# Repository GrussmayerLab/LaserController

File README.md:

# Laser Controller Project

## TL;DR (Quick Setup)

1. **Assemble the PCB**: 
   - Order the PCB from [JLCPCB](https://cart.jlcpcb.com) for ~$100 using the `gerber.zip`, `bom.csv`, and `laser_controller-top-pos.csv` files.
   - Use compatible [JST cables](https://www.amazon.nl/-/en/Mini-Micro-150mm-Cable-Female/dp/B01DU9OY40).

2. **Install MicroManager 2.0**:
   - Download and install [MicroManager 2.0](https://download.micro-manager.org/nightly/2.0/Windows/).

3. **Copy Files**:
   - Copy the precompiled `EMU` folder and `mmgr_dal_GrussmayerLab-LaserController.dll` into the root directory of MicroManager.

4. **Use the LaserControlGUI Plugin**:
   - Run MicroManager, open the **LaserControlGUI** plugin from **EMU**, and start controlling the laser!

---

This repository consists of the hardware, firmware, and software design for the Laser Controller system. It is divided into four main sections:

- **Electronics**: Schematic and PCB design files for the laser controller.
- **LaserControlFirmware**: C/C++ firmware for the Raspberry Pi Pico.
- **GrussmayerLab-LaserController**: C++ Micromanager Device Adapter to drive the laser controller.
- **LaserControlGUI**: Java-based plugin for Micromanager, built upon the EMU plugin.

## Table of Contents

- [Overview](#overview)
- [Folders](#folders)
  - [Electronics](#electronics)
  - [LaserControlFirmware](#lasercontrolfirmware)
  - [LaserControllerUI](#lasercontrollerui)
- [Getting Started](#getting-started)
  - [Hardware Setup](#hardware-setup)
  - [Firmware Setup](#firmware-setup)
  - [Software Setup](#software-setup)
- [Usage](#usage)
- [Contributing](#contributing)
- [License](#license)

## Overview

The Laser Controller project integrates hardware and software components to control a laser system. It consists of:

1. **Hardware**: Electronics, including a schematic and PCB design, for laser control.
2. **Firmware**: Raspberry Pi Pico firmware (C/C++) managing communication with the hardware.
3. **Software**: A Java plugin for MicroManager, based on the EMU plugin framework, along with a C++ Device Adapter for MicroManager.

## Folders

### Electronics

This folder contains the hardware designs for the laser controller:

- **Schematic**: Electrical design for the laser control system.
- **PCB Design**: Printed circuit board design files created using KiCAD.

Files in this folder:
- `schematic.kicad_sch`: Schematic file.
- `pcb.kicad_pcb`: PCB design file.

For more details, refer to the [KiCAD Documentation](https://kicad.org/documentation/).

### LaserControlFirmware

Firmware for the Raspberry Pi Pico, written in C/C++, responsible for controlling the laser system.

Files in this folder:
- `main.cpp`: Main program code.
- `CMakeLists.txt`: CMake configuration.
- `README.md`: Firmware setup instructions.

### LaserControlGUI

Java-based plugin for Micromanager, allowing control of the laser system.

Files in this folder:
- `LaserPanel.java`: Laser slide panel code.
- `MyFrame.java`: Main plugin UI containing multiple LaserPanel instances.
- `MyPlugin.java`: Main plugin class implementing the UIPlugin interface.

## Getting Started

### Hardware Setup

1. **Review Hardware Files**: Use KiCAD to view schematic and PCB design files in the `Electronics` folder.
2. **Assemble the PCB**: Using `gerber.zip`, `bom.csv`, and `laser_controller-top-pos.csv`, you can assemble your PCB at [JLCPCB](https://cart.jlcpcb.com) for approximately $100.
3. **Connect Components**: The board has **JST S3B-PH-K-S (LF)(SN)** connectors. Buy [compatible cables](https://www.amazon.nl/-/en/Mini-Micro-150mm-Cable-Female/dp/B01DU9OY40) and modify them as needed.

### Firmware Setup

1. **Flashing Precompiled Firmware**:
   - The compiled UF2 firmware is already included in the repository.
   - Hold the **BOOTSEL** button on the Raspberry Pi Pico, connect it to a PC via USB, and it will appear as a **USB drive**.
   - Copy the UF2 file to the drive, and the Pico is programmed.

2. **Optional: Building from Source**:
   If you wish to modify the firmware, install the following tools:
   - [Raspberry Pi Pico SDK](https://github.com/raspberrypi/pico-sdk)
   - [CMake](https://cmake.org/)
   - [ARM GCC Toolchain](https://developer.arm.com/tools-and-software/openSourceTools/gnu-toolchain/gnu-toolchain-r)

   Clone the repository and build:
   ```bash
   git clone https://github.com/GrussmayerLab/LaserController.git
   cd LaserControlFirmware
   mkdir build
   cd build
   cmake ..
   make
   ```

### Software Setup

1. **Install MicroManager 2.0**:
   - Download and install the latest version of [MicroManager 2.0](https://download.micro-manager.org/nightly/2.0/Windows/). Copy the precompiled `EMU` folder (provided) into the root directory of MicroManager.

2. **Install the EMU Plugin** (for source code editing):
   - If you wish to modify or extend the plugin, follow the instructions on how to install [EMU](https://jdeschamps.github.io/EMU-guide/):

3. **Install LaserControlGUI Plugin**:
   - To enable the LaserControlUI plugin, export the Java project from Eclipse into the EMU folder in MicroManager.

4. **Install the Device Adapter**:
   - Copy the `mmgr_dal_GrussmayerLab-LaserController.dll` file in the root directory of MicroManager.
   - If you need to configure or extend the device adapter, follow the [MicroManager Visual Studio setup guide](https://micro-manager.org/Visual_Studio_project_settings_for_device_adapters). After setting up your project, place `.h` files in the header folder and `.cpp` files in the source folder. Compile the project, and place the resulting `.dll` file in the root directory of MicroManager.

## Usage

1. Start MicroManager.
2. Open the **LaserControlGUI** plugin.
3. The plugin will interface with the Raspberry Pi Pico, allowing laser control via MicroManager.

## License

This project is licensed under the MIT License - see the LICENSE file for details.

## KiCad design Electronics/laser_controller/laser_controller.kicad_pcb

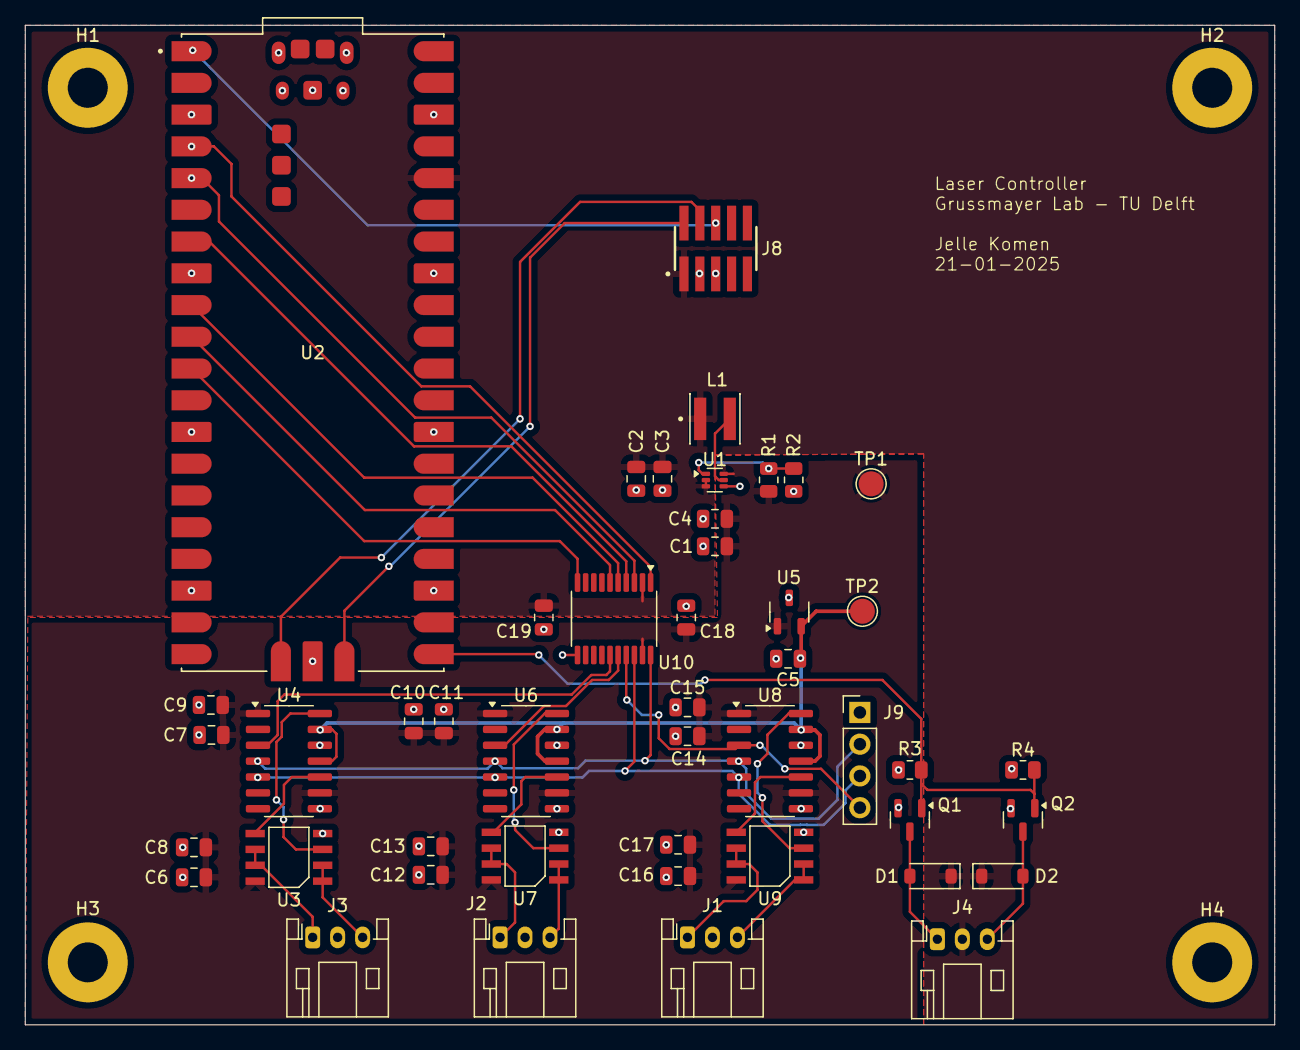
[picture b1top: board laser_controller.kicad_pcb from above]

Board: 2 copper layers, 100.0 x 80.0 mm, 50 parts (0 on the bottom side), 35 nets.

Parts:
C1, C3, C4, C5, C8, C9, C10, C12, C14, C16: 10u; C_0805_2012Metric
C2, C6, C7, C11, C13, C15, C17, C18, C19: 100n; C_0805_2012Metric
D1, D2: SM4007PL; D_SOD-123
H1, H2, H3, H4: MountingHole_Pad; MountingHole_3.2mm_M3_Pad
J1, J2, J3, J4: S3B-PH-K-S_LF__SN_; JST_PH_S3B-PH-K_1x03_P2.00mm_Horizontal
J8: FTSH-105-01-F-DV-P-TR; SAMTEC_FTSH-105-01-F-DV-P-TR
J9: Conn_01x04_Pin; PinHeader_1x04_P2.54mm_Vertical
L1: XEL4030-102MEC; IND_XEL4030-102MEC
Q1, Q2: AO3400A; SOT-23
R1: 820k; R_0805_2012Metric
R2: 100k; R_0805_2012Metric
R3, R4: 10k; R_0805_2012Metric
TP1: TEST +5V5; TestPoint_Pad_D2.0mm
TP2: TEST +2V5; TestPoint_Pad_D2.0mm
U1: TPS61023; SOT-563
U2: SC0915; MODULE_SC0915
U3, U7, U9: MCP6022; SOIC-8-SN
U4, U6, U8: MCP4922-ESL; SOIC-14_3.9x8.7mm_P1.27mm
U5: REF3025-AIDBZR; SOT-23-3
U10: TXS0108EPW; Texas_PW0020A_TSSOP-20_4.4x6.5mm_P0.65mm

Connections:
+2V5: C5.1, TP2.1, U4.11 (VrefB), U4.13 (VrefA), U5.2 (OUT), U6.11 (VrefB), U6.13 (VrefA), U8.11 (VrefB), U8.13 (VrefA)
+3.3V: C2.1, C3.1, C19.1, D1.1 (K), D2.1 (K), J4.2, J8.01, L1.1, U1.2 (EN), U1.3 (VIN), U2.36 (3V3_OUT), U10.2 (VCCA)
CLK: U2.4 (GP2), U10.1 (A1)
CLK_B: J9.2, U4.4 (SCK), U6.4 (SCK), U8.4 (SCK), U10.20 (B1)
CS_A: U2.7 (GP5), U10.4 (A3)
CS_A_B: J9.4, U8.3 (~CS), U10.17 (B3)
CS_B: U2.9 (GP6), U10.5 (A4)
CS_B_B: U6.3 (~CS), U10.16 (B4)
CS_C: U2.10 (GP7), U10.6 (A5)
CS_C_B: U4.3 (~CS), U10.15 (B5)
DAC_A0: J1.3, U9.1, U9.2 (-)
DAC_A1: J1.1, U9.6 (-), U9.7
DAC_B0: J2.3, U7.1, U7.2 (-)
DAC_B1: J2.1, U7.6 (-), U7.7
DAC_C0: J3.3, U3.1, U3.2 (-)
DAC_C1: J3.1, U3.6 (-), U3.7
GND: C1.2, C2.2, C3.2, C4.2, C5.2, C6.2, C7.2, C8.2, C9.2, C10.2, C11.2, C12.2, C13.2, C14.2, C15.2, C16.2, C17.2, C18.2, C19.2, H1.1, H2.1, H3.1, H4.1, J1.2, J2.2, J3.2, J8.03, J8.05, J9.1, Q1.2 (S), Q2.2 (S), R2.2, R3.2, R4.2, U1.4 (GND), U2.3 (GND), U2.8 (GND), U2.13 (GND), U2.18 (GND), U2.23 (GND), U2.28 (GND), U2.33 (AGND), U2.38 (GND), U2.A (USB_SHIELD), U2.B (USB_SHIELD), U2.C (USB_SHIELD), U2.D (USB_SHIELD), U2.D2 (GND), U2.TP1 (TP1_GND), U3.4 (V-), U4.8 (~LDAC), U4.12 (AVSS), U5.3 (GND), U6.8 (~LDAC), U6.12 (AVSS), U7.4 (V-), U8.8 (~LDAC), U8.12 (AVSS), U9.4 (V-), U10.11 (GND)
MOSI: U2.5 (GP3), U10.3 (A2)
MOSI_B: J9.3, U4.5 (SDI), U6.5 (SDI), U8.5 (SDI), U10.18 (B2)
Motor- A: D1.2 (A), J4.1, Q1.3 (D)
Motor- B: D2.2 (A), J4.3, Q2.3 (D)
unnamed: R1.2, R2.1, U1.1 (FB)
unnamed: L1.2, U1.5 (SW)
unnamed: U3.3 (+), U4.14 (VoutA)
unnamed: U3.5 (+), U4.10 (VoutB)
unnamed: U6.14 (VoutA), U7.3 (+)
unnamed: U6.10 (VoutB), U7.5 (+)
unnamed: U8.14 (VoutA), U9.3 (+)
unnamed: U8.10 (VoutB), U9.5 (+)
OE: U2.11 (GP8), U10.10 (OE)
PWM: Q1.1 (G), Q2.1 (G), R3.1, R4.1, U2.21 (GP16)
SWDCLK: J8.04, U2.D1 (SWCLK)
SWDIO: J8.02, U2.D3 (SWDIO)
SWO: J8.06, U2.1 (GP0)
VCC: C1.1, C4.1, C6.1, C7.1, C8.1, C9.1, C10.1, C11.1, C12.1, C13.1, C14.1, C15.1, C16.1, C17.1, C18.1, R1.1, TP1.1, U1.6 (VOUT), U3.8 (V+), U4.1 (VDD), U4.9 (~SHDN), U5.1 (IN), U6.1 (VDD), U6.9 (~SHDN), U7.8 (V+), U8.1 (VDD), U8.9 (~SHDN), U9.8 (V+), U10.19 (VCCB)

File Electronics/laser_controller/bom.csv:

"Comment","Designator","Footprint","LCSC"
"TXS0108EPW", "U10", "Package_SO:Texas_PW0020A_TSSOP-20_4.4x6.5mm_P0.65mm", "C17206"
"REF3025-AIDBZR","U5","Package_TO_SOT_SMD:SOT-23-3","C11334"
"MCP4922-ESL","U4,U6,U8","Package_SO:SOIC-14_3.9x8.7mm_P1.27mm","C39851"
"MCP6022","U3,U7,U9","Package_SO:SOIC-8_5.275x5.275mm_P1.27mm","C57639"
"TPS61023","U1","Package_TO_SOT_SMD:SOT-563","C919459"
"10k","R3,R4","Resistor_SMD:R_0805_2012Metric","C149504"
"100k","R2","Resistor_SMD:R_0805_2012Metric","C441992"
"820k","R1","Resistor_SMD:R_0805_2012Metric","C413229"
"AO3400A","Q1,Q2","Package_TO_SOT_SMD:SOT-23","C20917"
"XEL4030-102MEC","L1","parts:IND_XEL4030-102MEC","C5441341"
"FTSH-105-01-F-DV-P-TR","J8","parts:SAMTEC_FTSH-105-01-F-DV-P-TR","C5136979"
"SM4007PL","D1,D2","Diode_SMD:D_SOD-123","C64898"
"100n","C2,C6,C7,C11,C13,C15,C17,C18,C19","Capacitor_SMD:C_0805_2012Metric","C1711"
"10u","C1,C3,C4,C5,C8,C9,C10,C12,C14,C16","Capacitor_SMD:C_0805_2012Metric","C1713"
"S3B-PH-K-S_LF__SN_", "J1,J2,J3,J4","Connector_JST:JST_PH_S3B-PH-K_1x03_P2.00mm_Horizontal","C157929"

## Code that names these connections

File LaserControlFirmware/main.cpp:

#include "mcp4922.h"
#include <hardware/spi.h>
#include <hardware/pwm.h>
#include <stdio.h>
#include "pico/stdlib.h"
#include <string.h> // For memset

#define CLk_FREQ 100000
#define SCLK 2
#define MOSI 3
#define CS_C 5
#define CS_B 6
#define CS_A 7
#define OE 8
#define PWM 16
#define CMD_GET_DEVICE 0x01
#define CMD_SET_LASER 0x02
#define CMD_SET_MOTOR 0x03

#define START_FLAG 0x7E
#define END_FLAG 0x7F
#define DEVICE_ID 0x01
#define RESPONSE_ERROR 0xFF
#define BUFFER_SIZE 64
#define QUEUE_SIZE 10 // Number of messages in FIFO

// FIFO Queue for messages
typedef struct
{
    uint8_t data[BUFFER_SIZE];
    int length;
} Message;

Message fifo_queue[QUEUE_SIZE];
int fifo_head = 0;
int fifo_tail = 0;

uint8_t serial_buffer[BUFFER_SIZE];
int buffer_index = 0;

void checkAndExtractMessages();
void processSerialCommand();
uint8_t calculateCRC(uint8_t *args, int argCount);
void handleGetDevice();
void handleSetLaser(uint8_t channel_id, uint16_t value);
void handleSetMotor(uint16_t value);

MCP4922 dac1(spi0, CLk_FREQ, SCLK, MOSI, CS_A);
MCP4922 dac2(spi0, CLk_FREQ, SCLK, MOSI, CS_B);
MCP4922 dac3(spi0, CLk_FREQ, SCLK, MOSI, CS_C);

// FIFO Helper Functions
bool isFIFOFull() { return ((fifo_head + 1) % QUEUE_SIZE) == fifo_tail; }
bool isFIFOEmpty() { return fifo_head == fifo_tail; }

void enqueueMessage(uint8_t *data, int length)
{
    if (!isFIFOFull())
    {
        memcpy(fifo_queue[fifo_head].data, data, length);
        fifo_queue[fifo_head].length = length;
        fifo_head = (fifo_head + 1) % QUEUE_SIZE;
    }
}

bool dequeueMessage(Message *msg)
{
    if (!isFIFOEmpty())
    {
        *msg = fifo_queue[fifo_tail];
        fifo_tail = (fifo_tail + 1) % QUEUE_SIZE;
        return true;
    }
    return false;
}

int main(void)
{
    stdio_init_all();

    // Set stdin to non-blocking mode
    setvbuf(stdin, NULL, _IONBF, 0);

    printf("Pico USB Serial Ready\n");

    gpio_init(OE);
    gpio_set_dir(OE, GPIO_OUT);
    gpio_pull_up(OE);
    gpio_put(OE, 1);

    // uint16_t test = 0xFFF;

    // dac1.analogWrite(MCP4922::channel_B, test);
    // dac2.analogWrite(MCP4922::channel_B, test);
    // dac3.analogWrite(MCP4922::channel_B, test);

    while (true)
    {
        int ch = getchar_timeout_us(1); // Poll every 1us
        if (ch != -1)
        {
            serial_buffer[buffer_index++] = (uint8_t)ch;

            if (buffer_index >= BUFFER_SIZE)
            {
                buffer_index = 0; // Prevent overflow
            }

            // Extract messages from buffer and store them in FIFO
            checkAndExtractMessages();
        }

        // Process the next available command in FIFO
        if (!isFIFOEmpty())
        {
            processSerialCommand();
        }
    }
}

void checkAndExtractMessages()
{
    int startIdx = -1;
    int endIdx = -1;

    // Scan the buffer to find the first START_FLAG and END_FLAG
    for (int i = 0; i < buffer_index; i++)
    {
        if (serial_buffer[i] == START_FLAG && startIdx == -1)
        {
            startIdx = i; // Mark the start of a valid message
        }
        if (serial_buffer[i] == END_FLAG && startIdx != -1)
        {
            endIdx = i; // Found a complete message
            int messageLength = endIdx - startIdx + 1;

            // Store the valid message in FIFO
            enqueueMessage(&serial_buffer[startIdx], messageLength);

            // Remove processed message from buffer
            memmove(serial_buffer, &serial_buffer[endIdx + 1], BUFFER_SIZE - (endIdx + 1));
            buffer_index -= (endIdx + 1);

            // Reset start/end markers and continue scanning
            startIdx = -1;
            endIdx = -1;
            i = -1; // Restart loop from beginning
        }
    }

    // If buffer is full but no complete message, reset to prevent overflow
    if (buffer_index >= BUFFER_SIZE)
    {
        buffer_index = 0;
        memset(serial_buffer, 0, sizeof(serial_buffer));
    }
}

void processSerialCommand()
{
    Message msg;
    if (!dequeueMessage(&msg))
        return;

    uint8_t command, length, receivedCRC, calculatedCRC;
    uint8_t channel_id, upper, lower;
    uint16_t value;

    if (msg.length < 4)
        return; // Ignore incomplete packets

    command = msg.data[1];
    length = msg.data[2];
    receivedCRC = msg.data[length];

    // Validate CRC
    calculatedCRC = calculateCRC(&msg.data[1], length - 1);
    if (calculatedCRC != receivedCRC)
    {
        putchar(RESPONSE_ERROR);
        return;
    }

    switch (command)
    {
    case CMD_GET_DEVICE:
        handleGetDevice();
        break;
    case CMD_SET_LASER:
        channel_id = msg.data[3];
        upper = msg.data[4];
        lower = msg.data[5];
        value = (upper << 8) + lower;
        handleSetLaser(channel_id, value);
        break;
    case CMD_SET_MOTOR:
        upper = msg.data[3];
        lower = msg.data[4];
        value = (uint16_t)(upper << 8) + lower;
        handleSetMotor(value);
        break;
    default:
        putchar(RESPONSE_ERROR);
        break;
    }
}

uint8_t calculateCRC(uint8_t *args, int argCount)
{
    uint8_t crc = 0;
    for (int i = 0; i < argCount; i++)
    {
        crc ^= args[i];
    }
    return crc;
}

void handleGetDevice()
{
    uint8_t response[] = {CMD_GET_DEVICE, 0x01, DEVICE_ID};
    uint8_t crc = calculateCRC(response, 3);

    putchar(0x7E);
    for (int i = 0; i < 3; i++)
    {
        putchar(response[i]);
    }
    putchar(crc);
    putchar(0x7F);
}

void handleSetLaser(uint8_t channel_id, uint16_t value)
{
    // Array of DAC objects
    MCP4922 *dacs[] = {&dac1, &dac1, &dac2, &dac2, &dac3, &dac3};

    // Array of corresponding channels
    MCP4922::Channel channels[] = {
        MCP4922::channel_B, MCP4922::channel_A,
        MCP4922::channel_B, MCP4922::channel_A,
        MCP4922::channel_B, MCP4922::channel_A};

    if (channel_id < 6)
    {
        dacs[channel_id]->analogWrite(channels[channel_id], value);
    }
}

void setupPWM(uint gpio, uint16_t duty_cycle)
{
    // Get the slice number for this GPIO pin
    uint slice_num = pwm_gpio_to_slice_num(gpio);
    uint channel = pwm_gpio_to_channel(gpio);

    // Set GPIO function to PWM
    gpio_set_function(gpio, GPIO_FUNC_PWM);

    // Set the PWM frequency (125 MHz / wrap)
    pwm_set_wrap(slice_num, 65535); // 16-bit resolution (0-65535)

    // Set duty cycle
    pwm_set_chan_level(slice_num, channel, duty_cycle);

    // Enable PWM
    pwm_set_enabled(slice_num, true);
}

void handleSetMotor(uint16_t value)
{
    setupPWM(PWM, value);
}

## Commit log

2025-02-11 added readme to the firmware page
2025-02-11 added jar file
2025-02-27 fixed too many bugs
2025-03-11 added device controller c++ layer
2025-03-11 working pipeline...
2025-03-11 added device controller
2025-03-18 added compiled dll file
2025-03-24 dll 2019 toolset
2025-03-24 updated EMU
2025-06-23 remove laser 6
2025-08-28 working driver
